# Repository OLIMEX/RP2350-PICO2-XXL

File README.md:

# RP2350-PICO2-XXL
RP2350B PICO2 development board exposing 48 GPIO

https://www.olimex.com/Products/RaspberryPi/PICO/PICO2-XXL/

## Licensee
* Hardware is released under CERN Open Hardware Licence Version 2 - Strongly Reciprocal
* Software is released under GPL V3 Licensee
* Documentation is released under CC BY-SA 4.0

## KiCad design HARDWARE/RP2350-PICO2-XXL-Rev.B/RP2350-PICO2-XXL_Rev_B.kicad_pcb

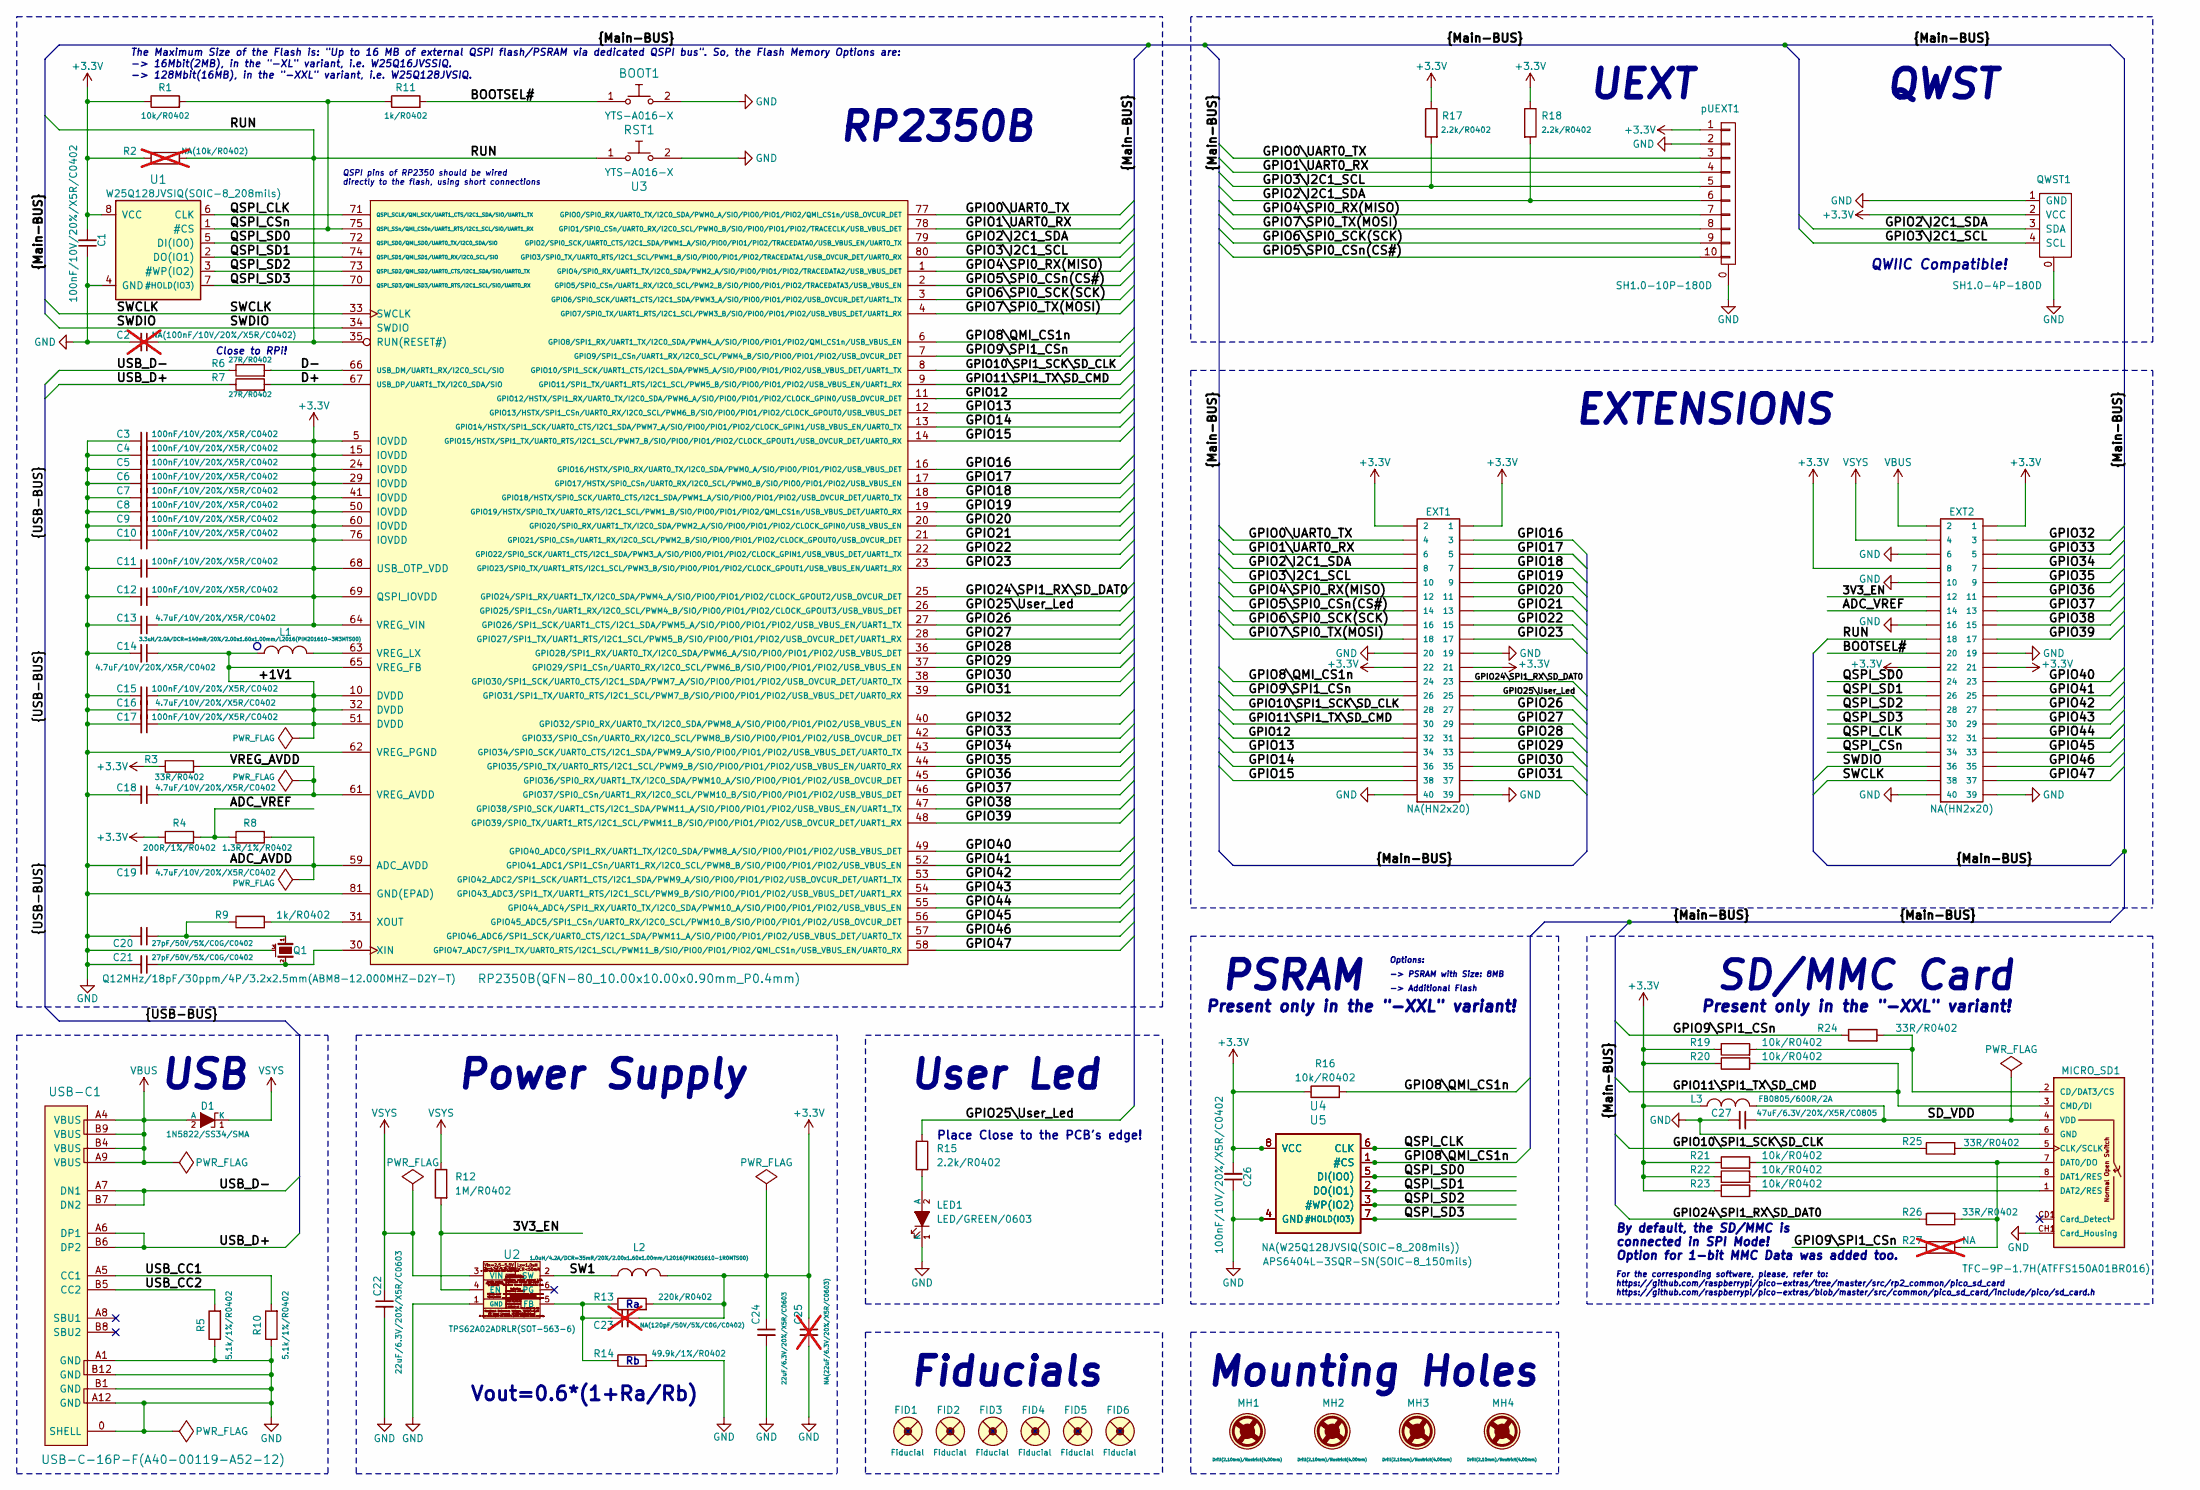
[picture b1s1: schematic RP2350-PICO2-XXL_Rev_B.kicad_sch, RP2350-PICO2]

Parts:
BOOT1: YTS-A016-X
C1, C3, C4, C5, C6, C7, C8, C9, C10, C11, C12, C15, C17, C26: 100nF/10V/20%/X5R/C0402; C_0402_5MIL_DWS
C2: NA(100nF/10V/20%/X5R/C0402); C_0402_5MIL_DWS; not fitted
C13, C14, C16, C18, C19: 4.7uF/10V/20%/X5R/C0402; C_0402_5MIL_DWS
C20, C21: 27pF/50V/5%/C0G/C0402; C_0402_5MIL_DWS
C22, C24: 22uF/6.3V/20%/X5R/C0603; C_0603_5MIL_DWS
C23: NA(120pF/50V/5%/C0G/C0402); C_0402_5MIL_DWS; not fitted
C25: NA(22uF/6.3V/20%/X5R/C0603); C_0603_5MIL_DWS; not fitted
C27: 47uF/6.3V/20%/X5R/C0805; C_0805_5MIL_DWS
D1: 1N5822/SS34/SMA; SMA-KA
EXT1, EXT2: NA(HN2x20); HN2x20
FID1, FID4: Fiducial; Fiducial1x3_Paste
FID2, FID3, FID5, FID6: Fiducial; Fiducial1x3
L1: 3.3uH/2.0A/DCR=140mR/20%/2.00x1.60x1.00mm/L2016(P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; L_2016_MM
L2: 1.0uH/4.2A/DCR=35mR/20%/2.00x1.60x1.00mm/L2016(PI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; L_2016_MM
L3: FB0805/600R/2A; L_0805_5MIL_DWS
LED1: LED/GREEN/0603; LED_0603_KA
MH1, MH2, MH3, MH4: Drill(2.10mm)/Restrict(4.00mm); Mounting_Hole_Drill-2.1mm_Clerance-4mm
MICRO_SD1: TFC-9P-1.7H(ATFFS150A01BR016); uSD(TFC-9P-1.xH(ATFFS150A01BR016))
Q1: Q12MHz/18pF/30ppm/4P/3.2x2.5mm(ABM8-12.000MHZ-D2Y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; TSX-3.2x2.5mm_GND(3)
QWST1: SH1.0-4P-180D; BM04B-SRSS-TB
R1, R16, R19, R20, R21, R22, R23: 10k/R0402; R_0402_5MIL_DWS
R2: NA(10k/R0402); R_0402_5MIL_DWS; not fitted
R3, R24, R25, R26: 33R/R0402; R_0402_5MIL_DWS
R4: 200R/1%/R0402; R_0402_5MIL_DWS
R5, R10: 5.1k/1%/R0402; R_0402_5MIL_DWS
R6, R7: 27R/R0402; R_0402_5MIL_DWS
R8: 1.3R/1%/R0402; R_0402_5MIL_DWS
R9, R11: 1k/R0402; R_0402_5MIL_DWS
R12: 1M/R0402; R_0402_5MIL_DWS
R13: 220k/R0402; R_0402_5MIL_DWS
R14: 49.9k/1%/R0402; R_0402_5MIL_DWS
R15, R17, R18: 2.2k/R0402; R_0402_5MIL_DWS
R27: NA; R_0402_5MIL_DWS; not fitted
RST1: YTS-A016-X
U1: W25Q128JVSIQ(SOIC-8_208mils); SO-8_208mil
U2: TPS62A02ADRLR(SOT-563-6); SOT-563-6
U3: RP2350B(QFN-80_10.00x10.00x0.90mm_P0.4mm); QFN-80_10.00x10.00x0.90mm_P0.4mm
U4: NA(W25Q128JVSIQ(SOIC-8_208mils)); SO-8_208mil
U5: APS6404L-3SQR-SN(SOIC-8_150mils); SO-8
USB-C1: USB-C-16P-F(A40-00119-A52-12); USB2.0_TYPE-C(A40-00119-A52-12)_Paste
pUEXT1: SH1.0-10P-180D; BM10B-SRSS-TB

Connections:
+3.3V: C1.2, C3.1, C4.1, C5.1, C6.1, C7.1, C8.1, C9.1, C10.1, C11.1, C12.1, C13.1, C23.2, C24.1, C25.1, C26.2, EXT1.1, EXT1.2, EXT1.21, EXT1.22, EXT2.1, EXT2.8, EXT2.21, EXT2.22, L2.1, L3.1, QWST1.2 (VCC), R1.1, R2.1, R3.1, R4.1, R13.2, R16.1, R17.1, R18.1, R19.1, R20.1, R21.1, R22.1, R23.1, U1.8 (VCC), U3.5 (IOVDD), U3.15 (IOVDD), U3.24 (IOVDD), U3.29 (IOVDD), U3.41 (IOVDD), U3.50 (IOVDD), U3.60 (IOVDD), U3.64 (VREG_VIN), U3.68 (USB_OTP_VDD), U3.69 (QSPI_IOVDD), U3.76 (IOVDD), U4.8 (VCC), U5.8 (VCC), pUEXT1.1
/3V3_EN: EXT2.12, R12.2, U2.4 (EN)
/+1V1: C14.1, C15.1, C16.1, C17.1, L1.1, U3.10 (DVDD), U3.32 (DVDD), U3.51 (DVDD), U3.65 (VREG_FB)
/ADC_AVDD: C19.1, R8.2, U3.59 (ADC_AVDD)
/ADC_VREF: EXT2.14, R4.2, R8.1
/BOOTSEL#: BOOT1.1, EXT2.20, R11.2
/D+: R7.2, U3.67 (USB_DP/UART1_TX/I2C0_SDA/SIO)
/D-: R6.2, U3.66 (USB_DM/UART1_RX/I2C0_SCL/SIO)
/GPIO0\UART0_TX: EXT1.4, U3.77 (GPIO0/SPI0_RX/UART0_TX/I2C0_SDA/PWM0_A/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), pUEXT1.3
/GPIO1\UART0_RX: EXT1.6, U3.78 (GPIO1/SPI0_CSn/UART0_RX/I2C0_SCL/PWM0_B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), pUEXT1.4
/GPIO2\I2C1_SDA: EXT1.8, QWST1.3 (SDA), R18.2, U3.79 (GPIO2/SPI0_SCK/UART0_CTS/I2C1_SDA/PWM1_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), pUEXT1.6
/GPIO3\I2C1_SCL: EXT1.10, QWST1.4 (SCL), R17.2, U3.80 (GPIO3/SPI0_TX/UART0_RTS/I2C1_SCL/PWM1_B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), pUEXT1.5
/GPIO4\SPI0_RX(MISO): EXT1.12, U3.1 (GPIO4/SPI0_RX/UART1_TX/I2C0_SDA/PWM2_A/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), pUEXT1.7
/GPIO5\SPI0_CSn(CS#): EXT1.14, U3.2 (GPIO5/SPI0_CSn/UART1_RX/I2C0_SCL/PWM2_B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), pUEXT1.10
/GPIO6\SPI0_SCK(SCK): EXT1.16, U3.3 (GPIO6/SPI0_SCK/UART1_CTS/I2C1_SDA/PWM3_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), pUEXT1.9
/GPIO7\SPI0_TX(MOSI): EXT1.18, U3.4 (GPIO7/SPI0_TX/UART1_RTS/I2C1_SCL/PWM3_B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), pUEXT1.8
/GPIO8\QMI_CS1n: EXT1.24, R16.2, U3.6 (GPIO8/SPI1_RX/UART1_TX/I2C0_SDA/PWM4_A/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), U4.1 (#CS), U5.1 (#CS)
/GPIO9\SPI1_CSn: EXT1.26, R24.1, R27.1, U3.7 (GPIO9/SPI1_CSn/UART1_RX/I2C0_SCL/PWM4_B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)
/GPIO10\SPI1_SCK\SD_CLK: EXT1.28, R25.1, U3.8 (GPIO10/SPI1_SCK/UART1_CTS/I2C1_SDA/PWM5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)
/GPIO11\SPI1_TX\SD_CMD: EXT1.30, MICRO_SD1.3 (CMD/DI), R20.2, U3.9 (GPIO11/SPI1_TX/UART1_RTS/I2C1_SCL/PWM5_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)
/GPIO12: EXT1.32, U3.11 (GPIO12/HSTX/SPI1_RX/UART0_TX/I2C0_SDA/P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)
/GPIO13: EXT1.34, U3.12 (GPIO13/HSTX/SPI1_CSn/UART0_RX/I2C0_SCL/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)
/GPIO14: EXT1.36, U3.13 (GPIO14/HSTX/SPI1_SCK/UART0_CTS/I2C1_SDA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)
/GPIO15: EXT1.38, U3.14 (GPIO15/HSTX/SPI1_TX/UART0_RTS/I2C1_SCL/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)
/GPIO16: EXT1.3, U3.16 (GPIO16/HSTX/SPI0_RX/UART0_TX/I2C0_SDA/P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)
/GPIO17: EXT1.5, U3.17 (GPIO17/HSTX/SPI0_CSn/UART0_RX/I2C0_SCL/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)
/GPIO18: EXT1.7, U3.18 (GPIO18/HSTX/SPI0_SCK/UART0_CTS/I2C1_SDA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)
/GPIO19: EXT1.9, U3.19 (GPIO19/HSTX/SPI0_TX/UART0_RTS/I2C1_SCL/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)
/GPIO20: EXT1.11, U3.20 (GPIO20/SPI0_RX/UART1_TX/I2C0_SDA/PWM2_A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)
/GPIO21: EXT1.13, U3.21 (GPIO21/SPI0_CSn/UART1_RX/I2C0_SCL/PWM2_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)
/GPIO22: EXT1.15, U3.22 (GPIO22/SPI0_SCK/UART1_CTS/I2C1_SDA/PWM3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)
/GPIO23: EXT1.17, U3.23 (GPIO23/SPI0_TX/UART1_RTS/I2C1_SCL/PWM3_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)
/GPIO24\SPI1_RX\SD_DAT0: EXT1.23, R26.1, U3.25 (GPIO24/SPI1_RX/UART1_TX/I2C0_SDA/PWM4_A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)
/GPIO25\User_Led: EXT1.25, R15.2, U3.26 (GPIO25/SPI1_CSn/UART1_RX/I2C0_SCL/PWM4_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)
/GPIO26: EXT1.27, U3.27 (GPIO26/SPI1_SCK/UART1_CTS/I2C1_SDA/PWM5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)
/GPIO27: EXT1.29, U3.28 (GPIO27/SPI1_TX/UART1_RTS/I2C1_SCL/PWM5_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)
/GPIO28: EXT1.31, U3.36 (GPIO28/SPI1_RX/UART0_TX/I2C0_SDA/PWM6_A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)
/GPIO29: EXT1.33, U3.37 (GPIO29/SPI1_CSn/UART0_RX/I2C0_SCL/PWM6_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)
/GPIO30: EXT1.35, U3.38 (GPIO30/SPI1_SCK/UART0_CTS/I2C1_SDA/PWM7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)
/GPIO31: EXT1.37, U3.39 (GPIO31/SPI1_TX/UART0_RTS/I2C1_SCL/PWM7_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)
/GPIO32: EXT2.3, U3.40 (GPIO32/SPI0_RX/UART0_TX/I2C0_SDA/PWM8_A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)
/GPIO33: EXT2.5, U3.42 (GPIO33/SPI0_CSn/UART0_RX/I2C0_SCL/PWM8_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)
/GPIO34: EXT2.7, U3.43 (GPIO34/SPI0_SCK/UART0_CTS/I2C1_SDA/PWM9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)
/GPIO35: EXT2.9, U3.44 (GPIO35/SPI0_TX/UART0_RTS/I2C1_SCL/PWM9_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)
/GPIO36: EXT2.11, U3.45 (GPIO36/SPI0_RX/UART1_TX/I2C0_SDA/PWM10_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)
/GPIO37: EXT2.13, U3.46 (GPIO37/SPI0_CSn/UART1_RX/I2C0_SCL/PWM10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)
/GPIO38: EXT2.15, U3.47 (GPIO38/SPI0_SCK/UART1_CTS/I2C1_SDA/PWM1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)
/GPIO39: EXT2.17, U3.48 (GPIO39/SPI0_TX/UART1_RTS/I2C1_SCL/PWM11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)
/GPIO40: EXT2.23, U3.49 (GPIO40_ADC0/SPI1_RX/UART1_TX/I2C0_SDA/P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)
/GPIO41: EXT2.25, U3.52 (GPIO41_ADC1/SPI1_CSn/UART1_RX/I2C0_SCL/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)
/GPIO42: EXT2.27, U3.53 (GPIO42_ADC2/SPI1_SCK/UART1_CTS/I2C1_SDA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)
/GPIO43: EXT2.29, U3.54 (GPIO43_ADC3/SPI1_TX/UART1_RTS/I2C1_SCL/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)
/GPIO44: EXT2.31, U3.55 (GPIO44_ADC4/SPI1_RX/UART0_TX/I2C0_SDA/P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)
/GPIO45: EXT2.33, U3.56 (GPIO45_ADC5/SPI1_CSn/UART0_RX/I2C0_SCL/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)
/GPIO46: EXT2.35, U3.57 (GPIO46_ADC6/SPI1_SCK/UART0_CTS/I2C1_SDA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)
/GPIO47: EXT2.37, U3.58 (GPIO47_ADC7/SPI1_TX/UART0_RTS/I2C1_SCL/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)
/QSPI_CLK: EXT2.32, U1.6 (CLK), U3.71 (QSPI_SCLK/QMI_SCK/UART1_CTS/I2C1_SDA/SI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), U4.6 (CLK), U5.6 (CLK)
/QSPI_CSn: EXT2.34, R1.2, R11.1, U1.1 (#CS), U3.75 (QSPI_SSn/QMI_CS0n/UART1_RTS/I2C1_SCL/SI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)
/QSPI_SD0: EXT2.24, U1.5 (DI(IO0)), U3.72 (QSPI_SD0/QMI_SD0/UART0_TX/I2C0_SDA/SIO), U4.5 (DI(IO0)), U5.5 (DI(IO0))
/QSPI_SD1: EXT2.26, U1.2 (DO(IO1)), U3.74 (QSPI_SD1/QMI_SD1/UART0_RX/I2C0_SCL/SIO), U4.2 (DO(IO1)), U5.2 (DO(IO1))
/QSPI_SD2: EXT2.28, U1.3 (#WP(IO2)), U3.73 (QSPI_SD2/QMI_SD2/UART0_CTS/I2C1_SDA/SIO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), U4.3 (#WP(IO2)), U5.3 (#WP(IO2))
/QSPI_SD3: EXT2.30, U1.7 (#HOLD(IO3)), U3.70 (QSPI_SD3/QMI_SD3/UART0_RTS/I2C1_SCL/SIO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), U4.7 (#HOLD(IO3)), U5.7 (#HOLD(IO3))
/RUN: C2.1, EXT2.18, R2.2, RST1.1, U3.35 (RUN(RESET#))
/SD_VDD: C27.1, L3.2, MICRO_SD1.4 (VDD)
/SW1: L2.2, U2.2 (SW)
/SWCLK: EXT2.38, U3.33 (SWCLK)
/SWDIO: EXT2.36, U3.34 (SWDIO)
/USB_CC1: R10.2, USB-C1.A5 (CC1)
/USB_CC2: R5.2, USB-C1.B5 (CC2)
/USB_D+: R7.1, USB-C1.A6 (DP1), USB-C1.B6 (DP2)
/USB_D-: R6.1, USB-C1.A7 (DN1), USB-C1.B7 (DN2)
/VREG_AVDD: C18.1, R3.2, U3.61 (VREG_AVDD)
GND: BOOT1.2, C1.1, C2.2, C3.2, C4.2, C5.2, C6.2, C7.2, C8.2, C9.2, C10.2, C11.2, C12.2, C13.2, C14.2, C15.2, C16.2, C17.2, C18.2, C19.2, C20.2, C21.2, C22.2, C24.2, C25.2, C26.1, C27.2, EXT1.19, EXT1.20, EXT1.39, EXT1.40, EXT2.6, EXT2.10, EXT2.16, EXT2.19, EXT2.39, EXT2.40, LED1.1 (K), MICRO_SD1.6 (GND), MICRO_SD1.CH1 (Card_Housing), Q1.3 (case), QWST1.0, QWST1.1 (GND), R5.1, R10.1, R14.2, RST1.2, U1.4 (GND), U2.1 (GND), U3.62 (VREG_PGND), U3.81 (GND(EPAD)), U4.4 (GND), U5.4 (GND), USB-C1.0 (SHELL), USB-C1.A1 (GND), USB-C1.A12 (GND), USB-C1.B1 (GND), USB-C1.B12 (GND), pUEXT1.0, pUEXT1.2
unnamed: C20.1, Q1.1, R9.1
unnamed: LED1.2 (A), R15.1
unnamed: MICRO_SD1.2 (CD/DAT3/CS), R19.2, R24.2
unnamed: MICRO_SD1.5 (CLK/SCLK), R25.2
unnamed: MICRO_SD1.7 (DAT0/DO), R21.2, R26.2, R27.2
unnamed: MICRO_SD1.8 (DAT1/RES), R22.2
unnamed: MICRO_SD1.1 (DAT2/RES), R23.2
unnamed: C23.1, R13.1, R14.1, U2.5 (FB)
unnamed: L1.2, U3.63 (VREG_LX)
unnamed: C21.1, Q1.2, U3.30 (XIN)
unnamed: R9.2, U3.31 (XOUT)
VBUS: D1.2 (A), EXT2.2, USB-C1.A4 (VBUS), USB-C1.A9 (VBUS), USB-C1.B4 (VBUS), USB-C1.B9 (VBUS)
VSYS: C22.1, D1.1 (K), EXT2.4, R12.1, U2.3 (VIN)

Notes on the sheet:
Present only in the "-XXL" variant!
EXTENSIONS
QSPI pins of RP2350 should be wired directly to the flash, using short connections
-> PSRAM with Size: 8MB
By default, the SD/MMC is connected in SPI Mode! Option for 1-bit MMC Data was added too.
The Maximum Size of the Flash is: "Up to 16 MB of external QSPI flash/PSRAM via dedicated QSPI bus". So, the Flash Memory Options are: -> 16Mbit(2MB), in the "-XL" variant, i.e. W25Q16JVSSIQ. -> 128Mbit(16MB), in the "-XXL" variant, i.e. W25Q128JVSIQ.
SD/MMC Card
QWST
USB
User Led
For the corresponding software, please, refer to: https://github.com/raspberrypi/pico-extras/tree/master/src/rp2_common/pico_sd_card https://github.com/raspberrypi/pico-extras/blob/master/src/common/pico_sd_card/include/pico/sd_card.h
Options:
-> Additional Flash
QWIIC Compatible!
Place Close to the PCB's edge!
Close to RPi!
RP2350B
Vout=0.6*(1+Ra/Rb)
Mounting Holes
Power Supply
PSRAM
Fiducials
UEXT

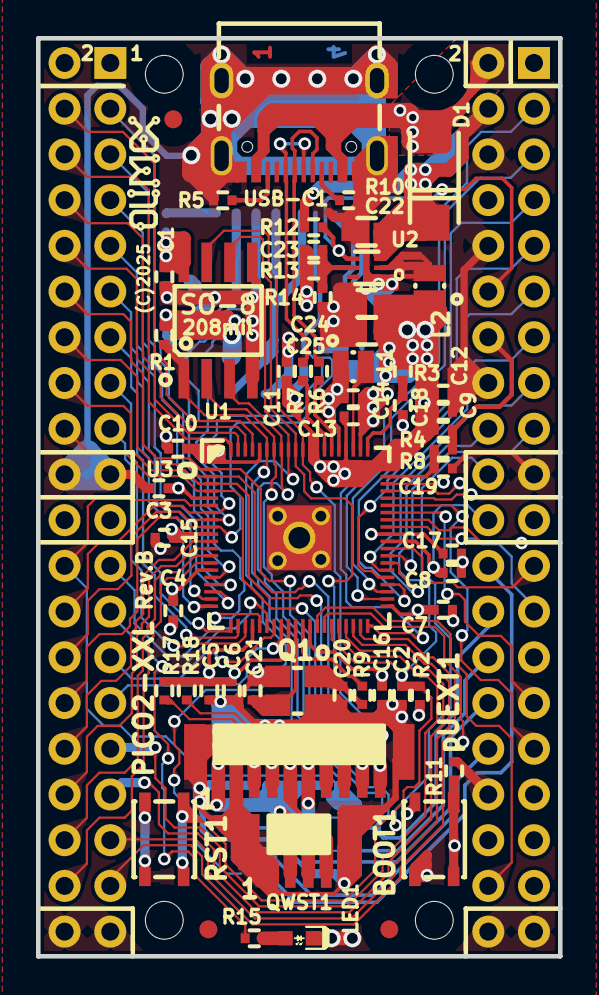
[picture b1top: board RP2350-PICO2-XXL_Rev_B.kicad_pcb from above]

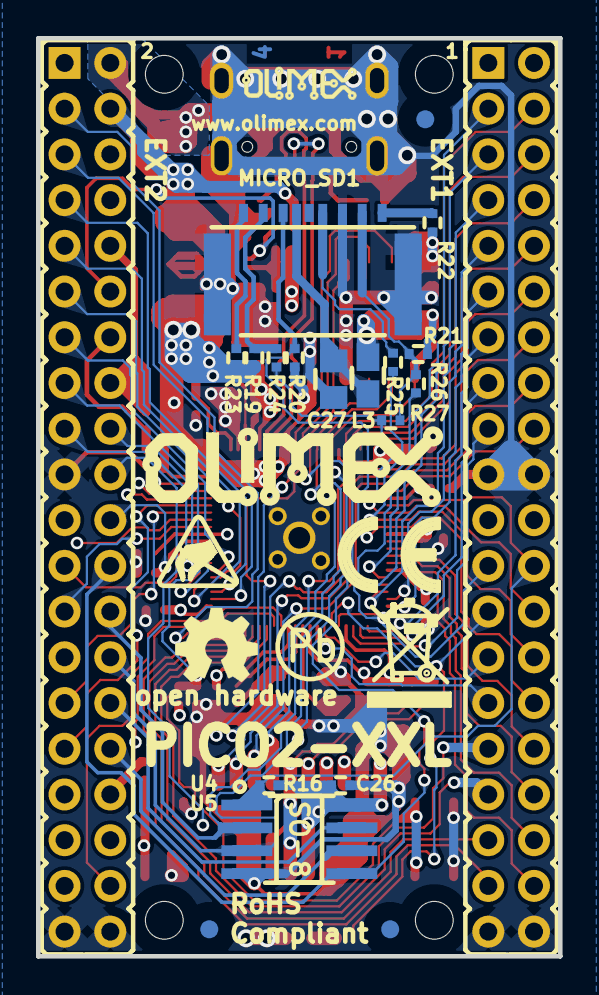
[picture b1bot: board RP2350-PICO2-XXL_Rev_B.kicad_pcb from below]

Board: 4 copper layers, 29.0 x 51.0 mm, 91 parts (28 on the bottom side), 86 nets.

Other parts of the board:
Logo_OLIMEX_80, Logo_OLIMEX_80-Bot: Logo_OLIMEX_80
Logo_OLIMEX_TB: Logo_OLIMEX_TB
Sign_Antistatic_Small: Sign_Antistatic; Sign_Antistatic_4.5mmX2.8mm
Sign_CE: CE_Sign
Sign_OSHW_7.3x6.0mm: Sign_OSHW_7.3x6.0mm; Sign_OSHW_7.3x6.0mmn
Sign_PB-Free: Sign_PB-Free
Sign_RecycleBin_1: Sign_RecycleBin_1

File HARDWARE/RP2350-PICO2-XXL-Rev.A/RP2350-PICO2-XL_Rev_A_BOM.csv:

Quantity,Value,Footprint,Reference
2,YTS-A016-X,YTS-A016-X,"BOOT1, RST1"
13,100nF/10V/20%/X5R/C0402,C_0402_5MIL_DWS,"C1, C3, C4, C5, C6, C7, C8, C9, C10, C11, C12, C15, C17"
5,4.7uF/10V/20%/X5R/C0402,C_0402_5MIL_DWS,"C13, C14, C16, C18, C19"
2,27pF/50V/5%/C0G/C0402,C_0402_5MIL_DWS,"C20, C21"
2,22uF/6.3V/20%/X5R/C0603,C_0603_5MIL_DWS,"C22, C24"
1,1N5822/SS34/SMA,SMA-KA,D1
1,3.3uH/2.0A/DCR=140mR/20%/2.00x1.60x1.00mm/L2016(PIM201610-3R3MTS00),L_2016_MM,L1
1,1.0uH/2.5A/DCR=30mR/20%/3.00x3.00x1.50mm/CD32(SWPA3015S1R0MT),CD32,L2
1,LED/GREEN/0603,LED_0603_KA,LED1
1,Q12MHz/18pF/30ppm/4P/3.2x2.5mm(ABM8-12.000MHZ-D2Y-T),TSX-3.2x2.5mm_GND(3),Q1
1,SH1.0-4P-180D,BM04B-SRSS-TB,QWST1
1,10k/R0402,R_0402_5MIL_DWS,R1
1,33R/R0402,R_0402_5MIL_DWS,R3
1,200R/1%/R0402,R_0402_5MIL_DWS,R4
2,5.1k/1%/R0402,R_0402_5MIL_DWS,"R5, R10"
2,27R/R0402,R_0402_5MIL_DWS,"R6, R7"
1,1.3R/1%/R0402,R_0402_5MIL_DWS,R8
2,1k/R0402,R_0402_5MIL_DWS,"R9, R11"
1,1M/R0402,R_0402_5MIL_DWS,R12
1,220k/R0402,R_0402_5MIL_DWS,R13
1,49.9k/1%/R0402,R_0402_5MIL_DWS,R14
3,2.2k/R0402,R_0402_5MIL_DWS,"R15, R17, R18"
1,W25Q16JVSSIQ,SO-8_208mil,U1
1,TPS62A02ADRLR(SOT-563-6),SOT-563-6,U2
1,RP2350B(QFN-80_10.00x10.00x0.90mm_P0.4mm),QFN-80_10.00x10.00x0.90mm_P0.4mm,U3
1,USB-C-16P-F(A40-00119-A52-12),USB2.0_TYPE-C(A40-00119-A52-12)_Paste,USB-C1
1,SH1.0-10P-180D,BM10B-SRSS-TB,pUEXT1

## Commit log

2025-01-16 update user manual
2025-04-15 Update
    Latest hardware revision and revision changes log
2025-04-15 Update
    Added uf2 files we program the boards.
2025-04-15 Update
    Spelling
2025-04-15 Features update
    Added pinout picture at the GitHub
2025-04-18 Update
    To fit hardware revision B

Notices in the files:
HARDWARE/RP2350-PICO2-XXL-Rev.B/RP2350-PICO2-XXL_Rev_B.kicad_pcb:
(C)2025
